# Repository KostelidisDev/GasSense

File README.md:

# GasSense

GasSense is an IoT project built on the NodeSense framework, featuring a gas sensor.

# License

[MIT License](./LICENSE)

# Disclaimer

This project was conducted as part of the course Ρ101: Embedded Systems in the M.Sc. program in Robotics, offered by the
Department of Computer, Informatics and Telecommunications Engineering at the International Hellenic University.

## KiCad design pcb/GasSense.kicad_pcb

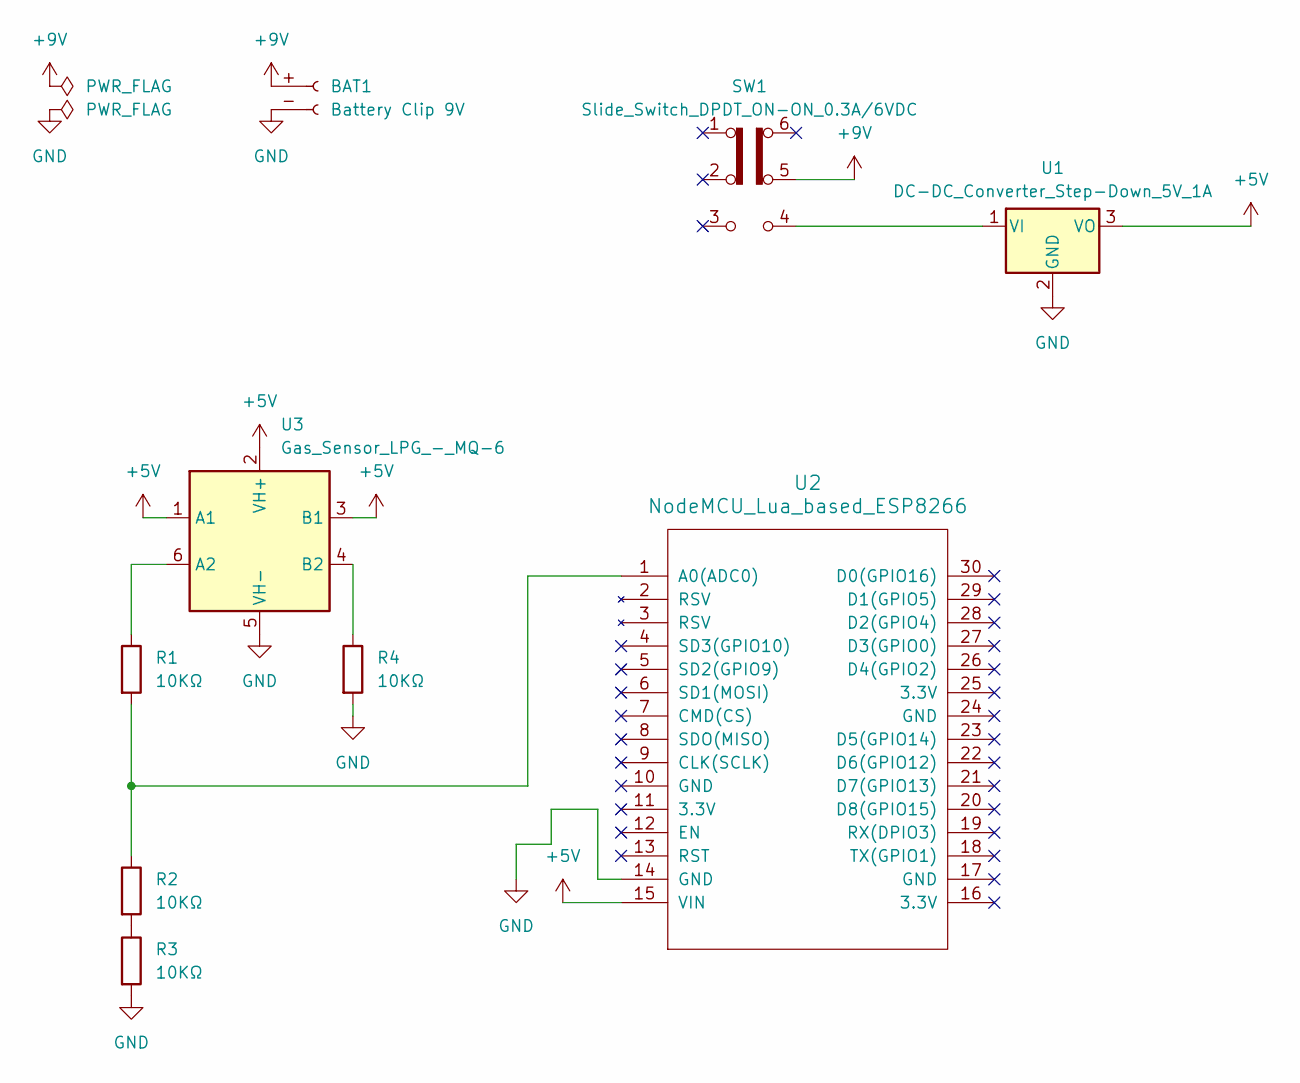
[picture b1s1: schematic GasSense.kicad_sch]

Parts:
BAT1: Battery Clip 9V; Battery_Clip_9V
R1, R2, R3, R4: 10ΚΩ; R_Axial_DIN0207_L6.3mm_D2.5mm_P7.62mm_Horizontal
SW1: Slide_Switch_DPDT_ON-ON_0.3A/6VDC; SW_CK_JS202011CQN_DPDT_Straight
U1: DC-DC_Converter_Step-Down_5V_1A; TO-220-3_Vertical
U2: NodeMCU_Lua_based_ESP8266; NodeMCU - Lua based ESP8266
U3: Gas_Sensor_LPG_-_MQ-6; Gas Sensor LPG - MQ-6

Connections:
+5V: U1.3 (VO), U2.15 (VIN), U3.1 (A1), U3.2 (VH+), U3.3 (B1)
+9V: BAT1.+ (Pin_1), SW1.5 (B)
GND: BAT1.- (Pin_2), R3.2, R4.2, U1.2 (GND), U2.14 (GND), U3.5 (VH-)
unnamed: R2.2, R3.1
unnamed: SW1.4 (A), U1.1 (VI)
unnamed: R1.2, R2.1, U2.1 (A0(ADC0))
unnamed: R1.1, U3.6 (A2)
unnamed: R4.1, U3.4 (B2)

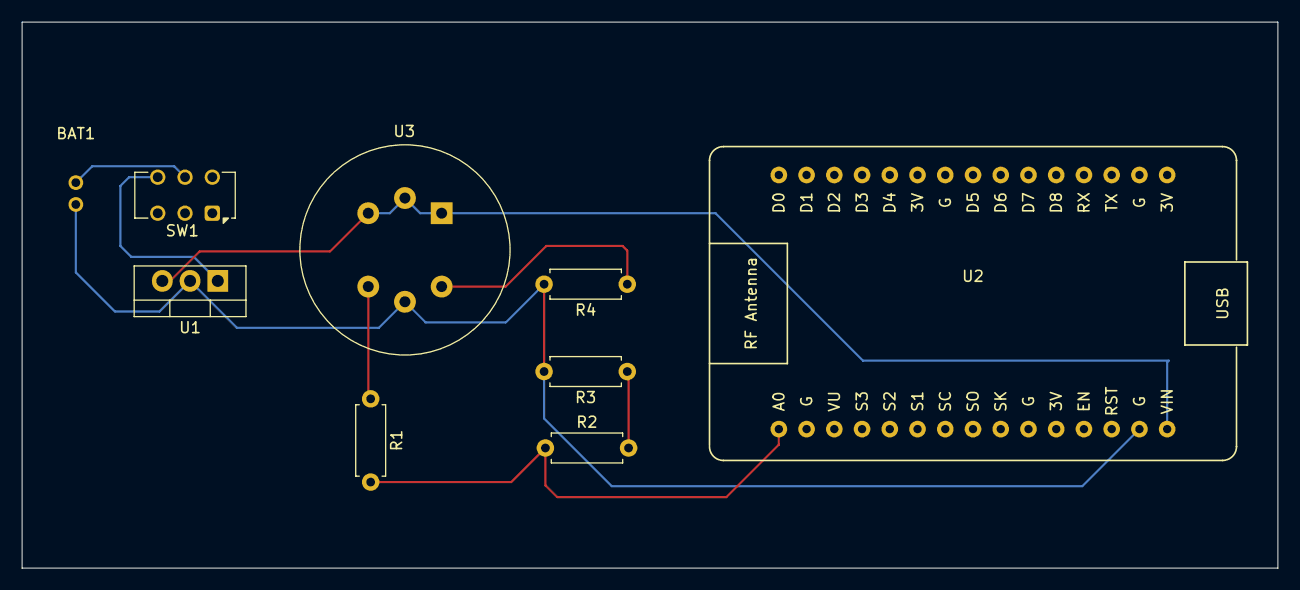
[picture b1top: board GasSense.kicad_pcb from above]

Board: 2 copper layers, 115.0 x 50.0 mm, 9 parts (0 on the bottom side), 8 nets.

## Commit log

2024-12-23 update env variables
2024-12-23 add support for light sensor
2024-12-23 Remove .DS_Store files and ignore them
2024-12-23 Remove WIFI credentials from logs
2024-12-23 add platform info and more logs
2025-01-06 add KiCad project (schematic and pcb)
2025-01-31 update schematic
